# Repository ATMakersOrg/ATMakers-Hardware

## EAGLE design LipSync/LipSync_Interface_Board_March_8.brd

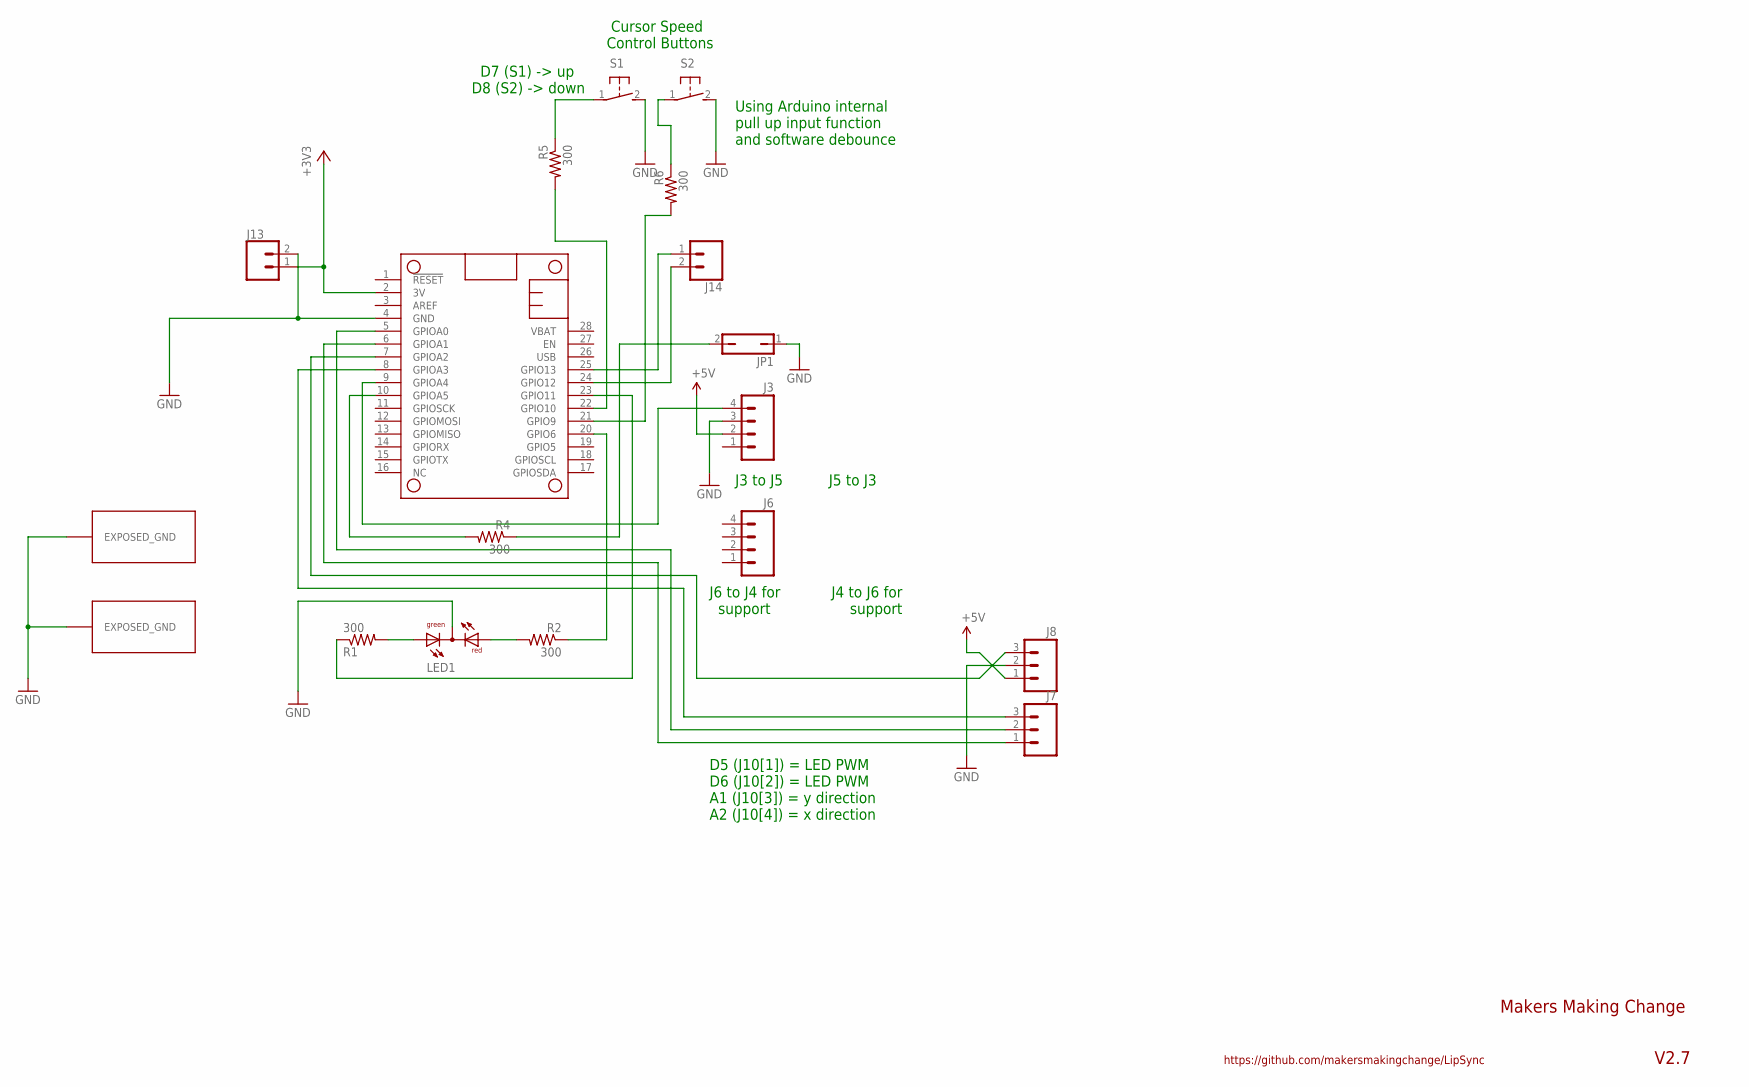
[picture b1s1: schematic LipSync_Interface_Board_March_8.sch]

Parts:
J3, J6: M04PTH; 1X04
J7, J8: M03LOCK; 1X03_LOCK
J13, J14: CONN_02; 1X02
JP1: JP1Q; JP1
LED1: DUOLED-RG-C; DUOLED-C-5MM
MS2: FEATHERWING_NODIM; FEATHERWING_DIM
R1, R2, R4, R5, R6: 300; AXIAL-0.3
S1, S2: 31-XXB3F-31XX-CUSTOM; B3F-31XX-CUSTOM
U$2, U$3: EXPOSED_GND

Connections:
+3V3: J13.1, MS2.2 (3V)
GND: J3.3, J8.2, J13.2, JP1.1, LED1.C, MS2.4 (GND), S1.2 (S), S2.2 (S), U$2.GND1, U$3.GND1
unnamed: J7.2, MS2.5 (GPIOA0)
unnamed: J7.1, MS2.6 (GPIOA1)
unnamed: J8.3, MS2.7 (GPIOA2)
unnamed: J7.3, MS2.8 (GPIOA3)
unnamed: J3.4, MS2.9 (GPIOA4)
unnamed: MS2.21 (GPIO9), R6.P$2 (2)
unnamed: MS2.20 (GPIO6), R2.P$1 (1)
unnamed: MS2.10 (GPIOA5), R4.P$2 (2)
unnamed: R5.P$1 (1), S1.1
unnamed: LED1.AX (AG), R1.P$2 (2)
unnamed: LED1.AR, R2.P$2 (2)
unnamed: JP1.2, R4.P$1 (1)
unnamed: R6.P$1 (1), S2.1
unnamed: J14.1, MS2.25 (GPIO13)
unnamed: MS2.23 (GPIO11), R1.P$1 (1)
unnamed: J14.2, MS2.24 (GPIO12)
unnamed: MS2.22 (GPIO10), R5.P$2 (2)
VCC: J3.2, J8.1

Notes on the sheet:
J6 to J4 for support
J4 to J6 for support
D5 (J10[1]) = LED PWM D6 (J10[2]) = LED PWM A1 (J10[3]) = y direction A2 (J10[4]) = x direction
J5 to J3
J3 to J5
Cursor Speed Control Buttons
D7 (S1) -> up D8 (S2) -> down
Using Arduino internal pull up input function and software debounce
Makers Making Change
V2.7
https://github.com/makersmakingchange/LipSync

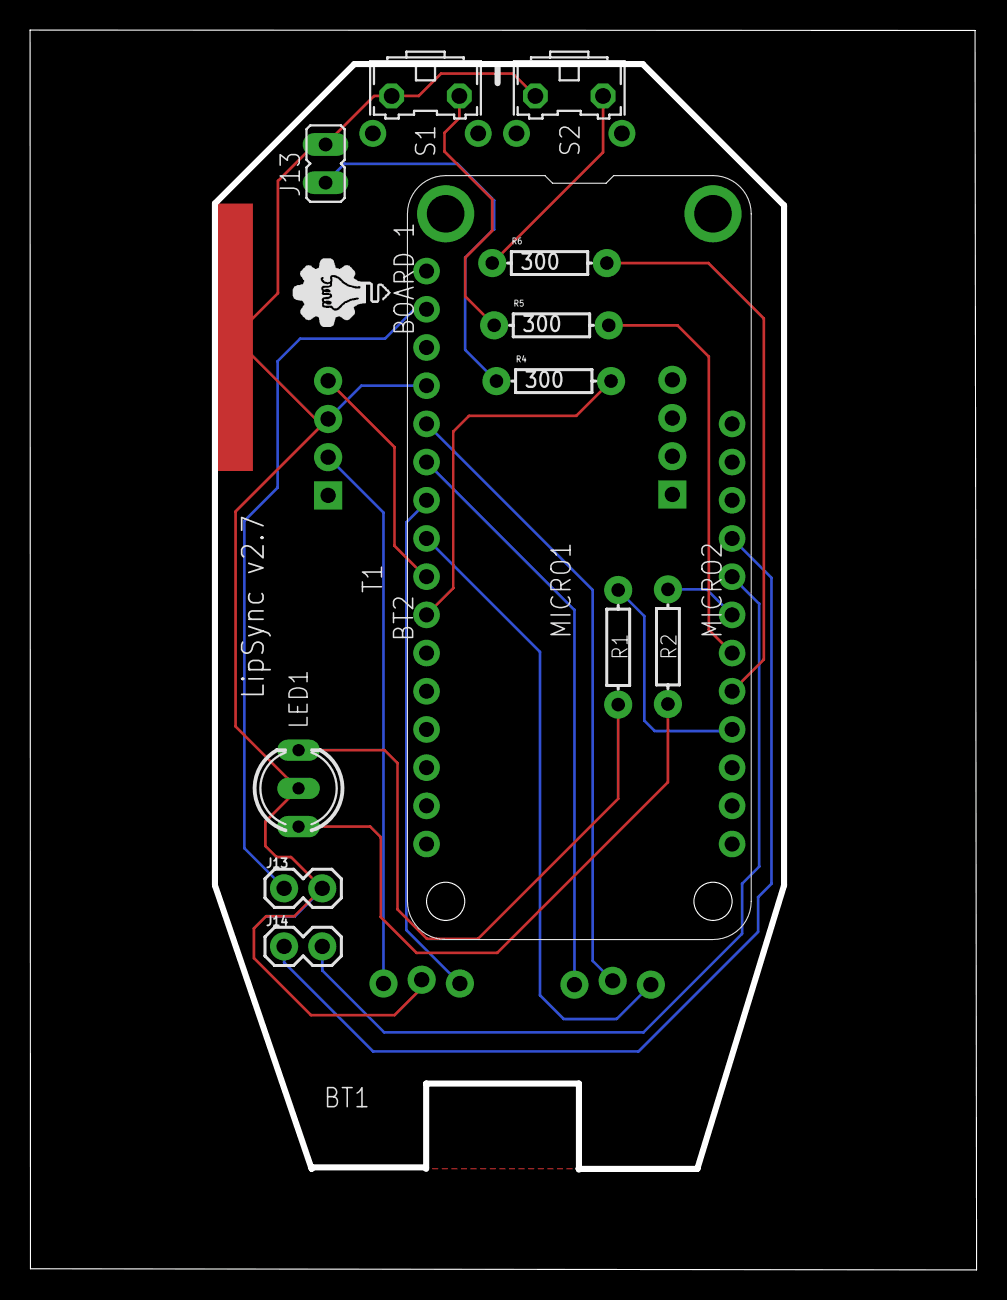
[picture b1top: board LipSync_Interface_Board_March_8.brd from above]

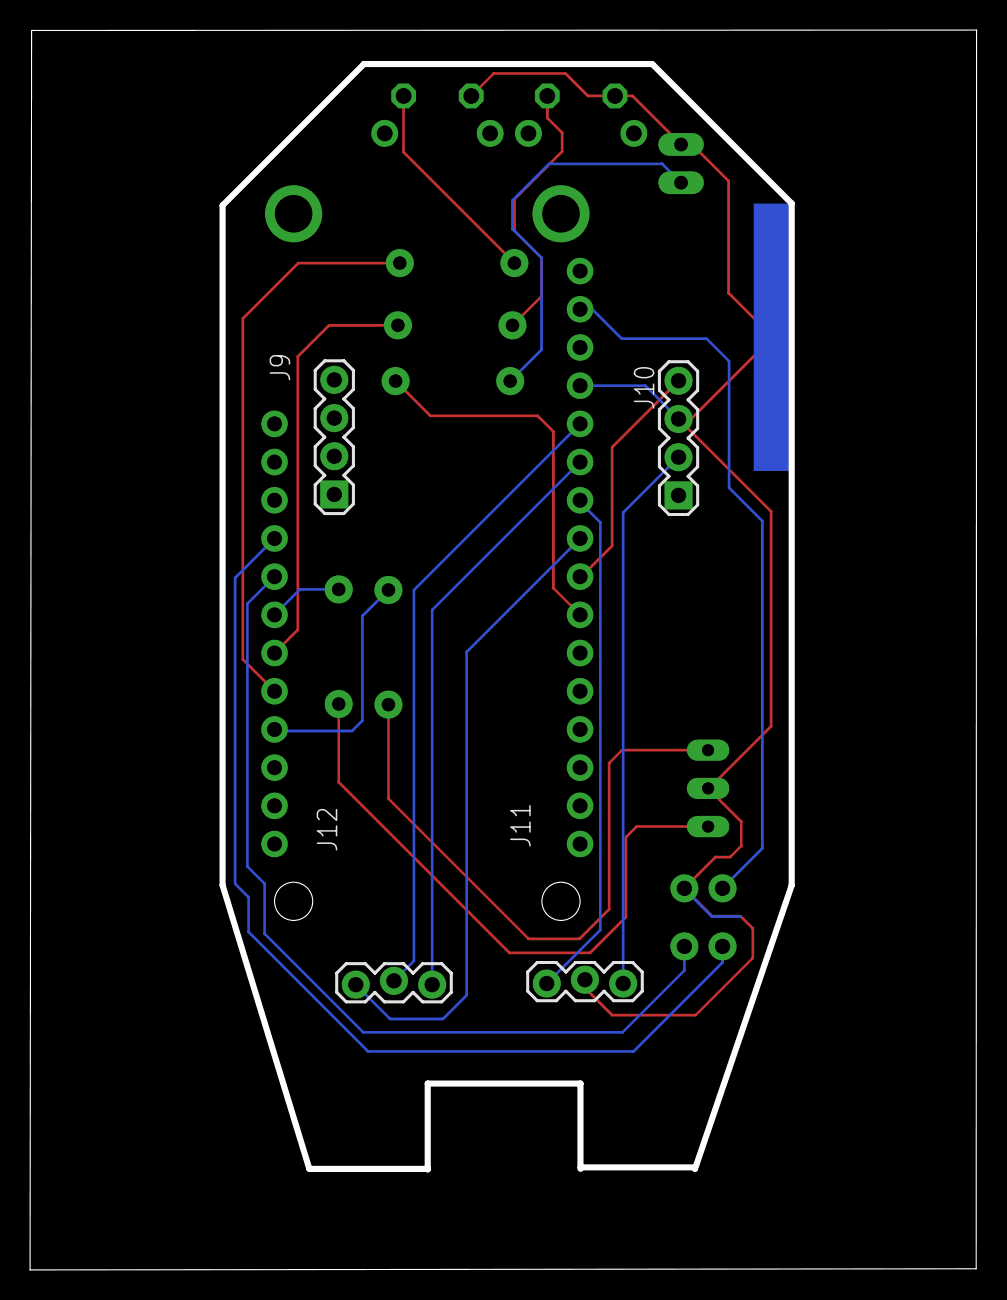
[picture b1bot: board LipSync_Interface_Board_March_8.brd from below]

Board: 2 copper layers, 62.9 x 82.4 mm, 18 parts (5 on the bottom side), 20 nets.

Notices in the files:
parts and their libraries:
SparkFun-Connectors: Licensing: Creative Commons ShareAlike 4.0 International - https://creativecommons.org/licenses/by-sa/4.0
